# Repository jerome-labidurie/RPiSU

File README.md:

INSTALL:

* Make your own PCB
* Burn firmware
* Connect wires (take a look in PCB files)
* Press On/Off button to start Raspberry Pi
* Copy RPiSU.sh to users home dir
* Execute 'sudo chmod 766 /home/users home dir/RPiSU.sh'
* Add command '/home/user/RPiSU.sh &' above 'exit 0' in /etc/rc.local
* Reboot

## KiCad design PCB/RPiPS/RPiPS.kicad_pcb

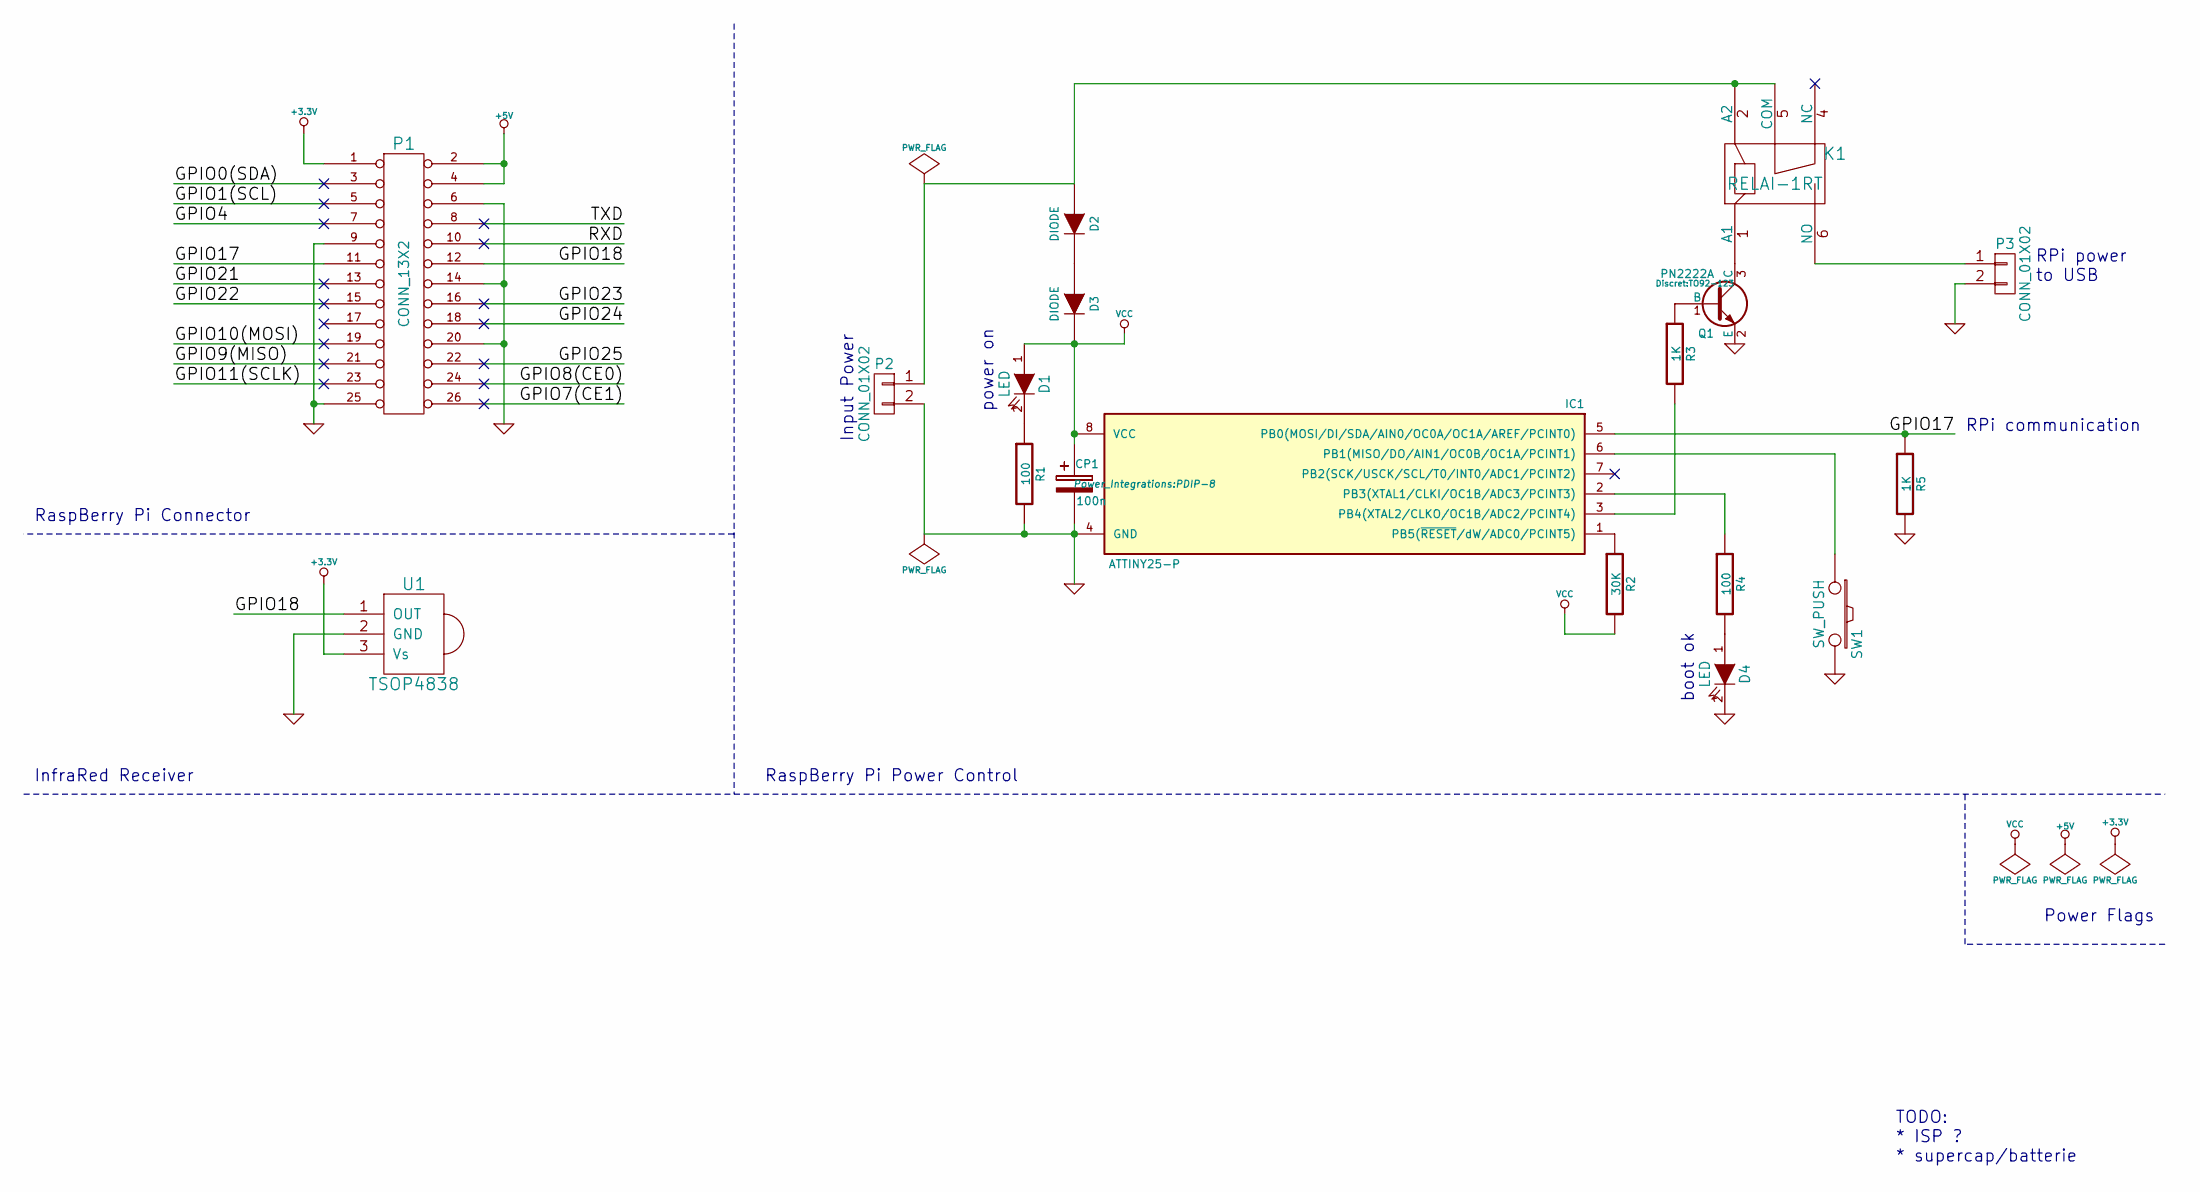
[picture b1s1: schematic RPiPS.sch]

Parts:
CP1: 100n; Elko_vert_DM5_RM2-5
D1, D4: LED; LED-5MM
D2, D3: DIODE; Diode_DO-35_SOD27_Horizontal_RM10
IC1: ATTINY25-P; PDIP-8
K1: RELAI-1RT; Relay_V23040
P1: CONN_13X2; pin_array_2x13
P2, P3: CONN_01X02; bornier2
Q1: PN2222A; TO92-123
R1, R4: 100; Resistor_Horizontal_RM10mm
R2: 30K; Resistor_Horizontal_RM10mm
R3, R5: 1K; Resistor_Horizontal_RM10mm
SW1: SW_PUSH
U1: TSOP4838

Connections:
+3.3V: P1.1, U1.3 (Vs)
+5V: P1.2, P1.4
/GPIO0(SDA): P1.3
/GPIO1(SCL): P1.5
/GPIO4: P1.7
/GPIO7(CE1): P1.26 (P22)
/GPIO8(CE0): P1.24 (P20)
/GPIO9(MISO): P1.21
/GPIO10(MOSI): P1.19
/GPIO11(SCLK): P1.23
/GPIO17: IC1.5 (PB0(MOSI/DI/SDA/AIN0/OC0A/OC1A/AREF/PCI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), P1.11, R5.1
/GPIO18: P1.12, U1.1 (OUT)
/GPIO21: P1.13
/GPIO22: P1.15
/GPIO23: P1.16
/GPIO24: P1.18
/GPIO25: P1.22
/RXD: P1.10
/TXD: P1.8
GND: CP1.2, D4.2 (K), IC1.4 (GND), P1.6, P1.9, P1.14, P1.20, P1.25 (P24), P2.2, P3.2, Q1.2 (E), R1.2, R5.2, SW1.2, U1.2 (GND)
unnamed: D1.2 (K), R1.1
unnamed: D2.1 (A), K1.2 (A2), K1.5 (COM), P2.1
unnamed: D2.2 (K), D3.1 (A)
unnamed: D4.1 (A), R4.2
unnamed: IC1.1 (PB5(~RESET~/dW/ADC0/PCINT5)), R2.1
unnamed: IC1.2 (PB3(XTAL1/CLKI/OC1B/ADC3/PCINT3)), R4.1
unnamed: IC1.3 (PB4(XTAL2/CLKO/OC1B/ADC2/PCINT4)), R3.2
unnamed: IC1.6 (PB1(MISO/DO/AIN1/OC0B/OC1A/PCINT1)), SW1.1
unnamed: K1.1 (A1), Q1.3 (C)
unnamed: K1.6 (NO), P3.1
unnamed: Q1.1 (B), R3.1
VCC: CP1.1, D1.1 (A), D3.2 (K), IC1.8 (VCC), R2.2

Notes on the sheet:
RPi power to USB
RPi communication
Input Power
TODO: * ISP ? * supercap/batterie
InfraRed Receiver
RaspBerry Pi Power Control
RaspBerry Pi Connector
Power Flags
power on
boot ok

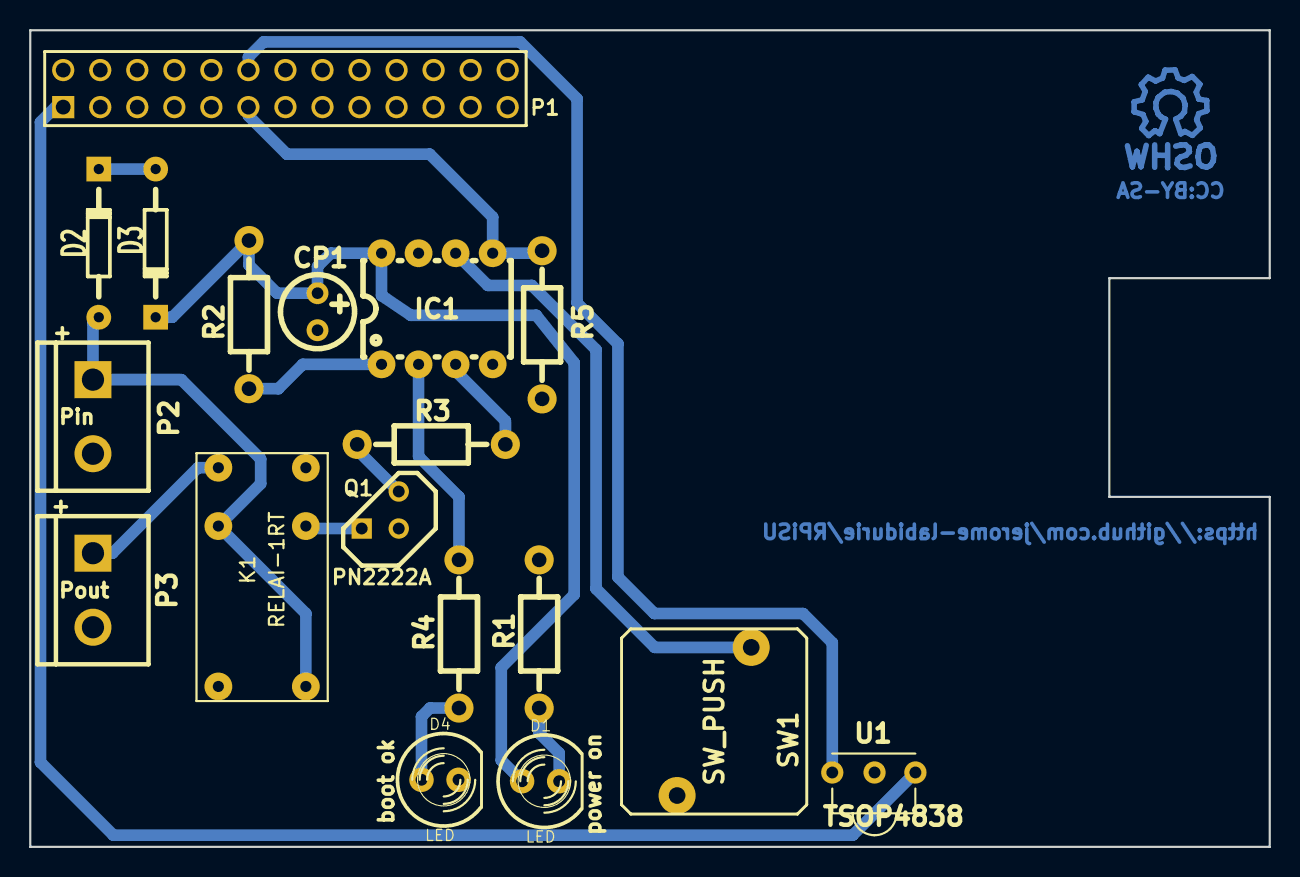
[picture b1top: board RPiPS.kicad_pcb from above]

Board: 2 copper layers, 85.0 x 56.0 mm, 19 parts (1 on the bottom side), 17 nets.

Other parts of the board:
SYM: Symbol_OSHW-Logo_CopperTop_07Jul2012; Symbol_OSHW-Logo_CopperTop

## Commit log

2013-05-16 Add install instructions
2013-07-16 Export exist check added
    If script executed, you get an error (line 3). Now the script check if gpio already exported
2014-01-05 Ignore unecessary files
2014-01-05 New scheme using Kicad
2014-01-08 Typon
2014-09-27 Move to RPi Expansion board template
2014-09-28 add IR receiver pcb routing fabrication files
2014-09-28 OSHW logo relay footprint
2014-09-29 add svg logo
2014-09-29 remove gnd plane over Pi connectors reverse P2 (1 is +) minor Silk adjustment
